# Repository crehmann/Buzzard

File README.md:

# Buzzard

Buzzard is a 40 keys ergonomic split keyboard. The layout is inspired by the [Architeuthis dux](https://github.com/tapioki/cephalopoda/tree/main/Architeuthis%20dux) with pinky, ring, index, and inner columns splayed at 15, 5, 0, -5, -5 degrees. However, it as two additional pinky keys and a modified thumb cluster.

## Features

- Integrated TrackPoint reset circuit and two possible positions to mount a TrackPoint to the bottom of the PCB. Either between the two inner columns or between the index and middle finger columns
- Mounting option for a linear actuator ([HapticBuzz from pimoroni](https://shop.pimoroni.com/products/drv2605l-linear-actuator-haptic-breakout))
- I2C interface for an OLED display
- Wireless Ready (however, without TrackPoint / linear actuator support):
  - Battery switch / connector
  - Option to use a battery friendly Sharp memory display instead of an OLED display
- Choc-spaced
- Partially hot swap sockets supported (not around the TrackPoint  module)
- Either surface mount or through hole components can be used

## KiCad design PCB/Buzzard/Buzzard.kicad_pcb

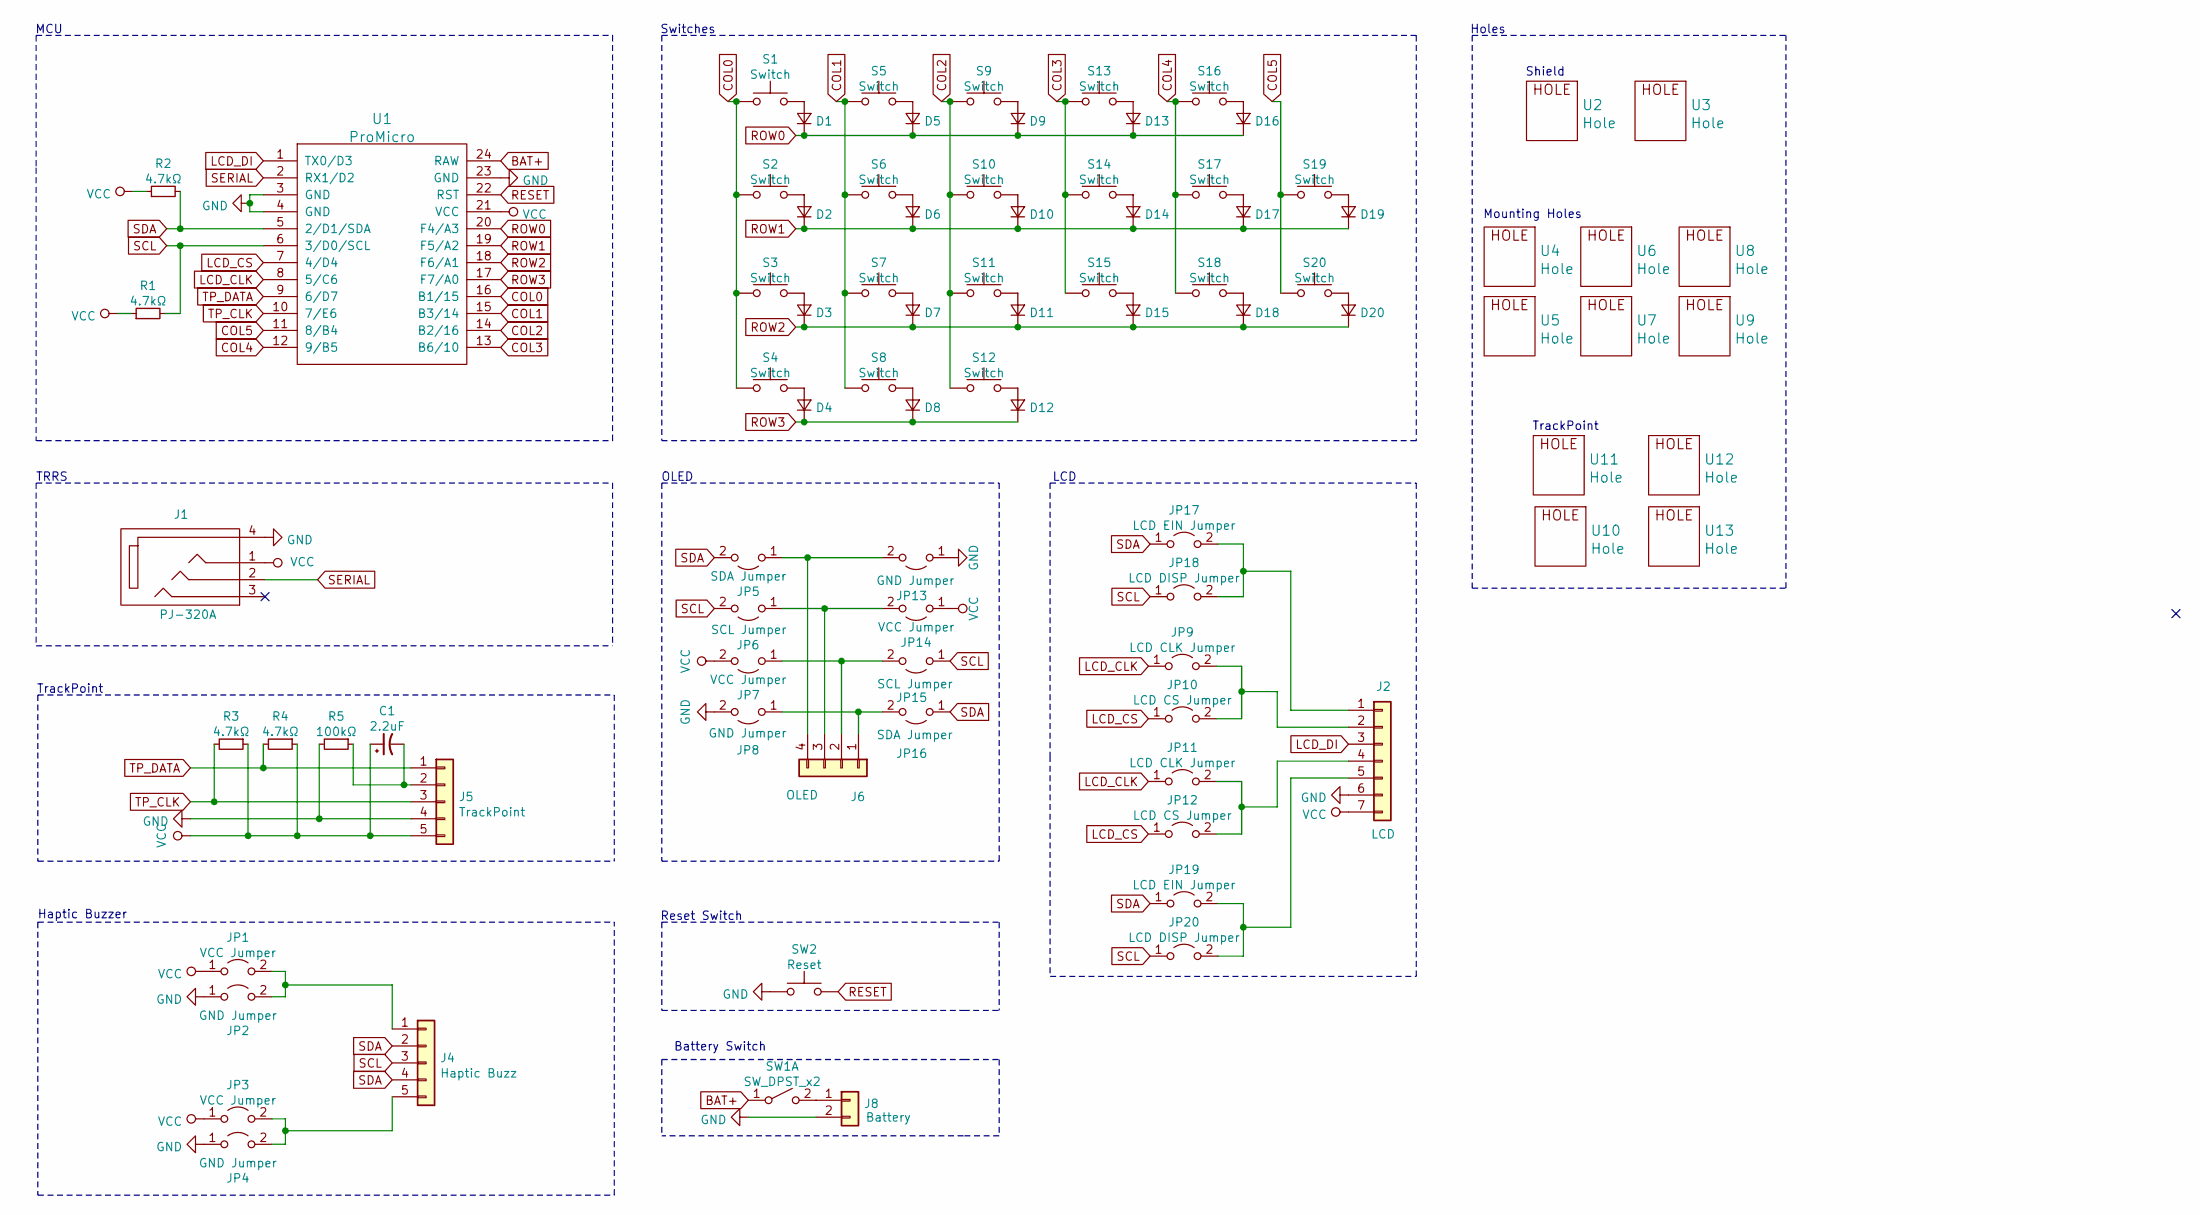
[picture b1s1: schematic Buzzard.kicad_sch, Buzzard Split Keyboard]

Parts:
C1: 2.2uF; C_THT_SMD_0805_HandSolder_Reversable
D1, D2, D3, D4, D5, D6, D7, D8, D9, D10, D11, D12, D13, D14, D15, D16, D17, D18, D19, D20: D_Small; D3_TH_SMD_v2
J1: PJ-320A; MJ-4PP-9
J2: LCD; SharpMemoryLcdBreakout-Reversable
J4: Haptic Buzz; Pimoroni Haptic Buzz DRV2605L Driver
J5: TrackPoint; PinHeader_1x05_P2.54mm_Vertical
J6: OLED
J8: Battery; JST_PH_S2B-PH-K_1x02_P2.00mm_Horizontal
JP1, JP3, JP7, JP14: VCC Jumper; SolderJumper-2_P1.3mm_Open_Pad1.0x1.5mm
JP2, JP4, JP8, JP13: GND Jumper; SolderJumper-2_P1.3mm_Open_Pad1.0x1.5mm
JP5, JP16: SDA Jumper; SolderJumper-2_P1.3mm_Open_Pad1.0x1.5mm
JP6, JP15: SCL Jumper; SolderJumper-2_P1.3mm_Open_Pad1.0x1.5mm
JP9, JP11: LCD CLK Jumper; SolderJumper-2_P1.3mm_Open_Pad1.0x1.5mm
JP10, JP12: LCD CS Jumper; SolderJumper-2_P1.3mm_Open_Pad1.0x1.5mm
JP17, JP19: LCD EIN Jumper; SolderJumper-2_P1.3mm_Open_Pad1.0x1.5mm
JP18, JP20: LCD DISP Jumper; SolderJumper-2_P1.3mm_Open_Pad1.0x1.5mm
R1, R2, R3, R4: 4.7kΩ; Resistor-TH_SMD
R5: 100kΩ; Resistor-TH_SMD
S1, S5, S6, S9, S10: Switch; SW_PG1350_reversible
S2, S3, S4, S7, S8, S11, S12, S13, S14, S15, S16, S17, S18, S19, S20: Switch; Kailh_socket_PG1350_optional_reversible.kicad_mod
SW1: SW_DPST_x2; SW-TH_3P-L9.1-W3.5-P2.50-S3.20-A3
SW2: Reset; SW_Tactile_SPST_Angled_PTS645Vx39-2LFS
U1: ProMicro; ProMicro_v2
U2, U3: Hole; M2_HOLE_PCB
U4, U5, U6, U7, U8, U9, U10, U11, U12, U13: Hole; HOLE_M2_TH

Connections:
BAT+: SW1.1 (A), U1.24 (RAW)
COL0: S1.1, S2.1, S3.1, S4.1, U1.16 (B1/15)
COL1: S5.1, S6.1, S7.1, S8.1, U1.15 (B3/14)
COL2: S9.1, S10.1, S11.1, S12.1, U1.14 (B2/16)
COL3: S13.1, S14.1, S15.1, U1.13 (B6/10)
COL4: S16.1, S17.1, S18.1, U1.12 (9/B5)
COL5: S19.1, S20.1, U1.11 (8/B4)
GND: J1.4, J2.6, J5.4, J8.2, JP2.1 (A), JP4.1 (A), JP8.2 (B), JP13.1 (A), R5.2, SW2.1, U1.3 (GND), U1.4 (GND), U1.23 (GND)
LCD_CLK: JP9.1 (A), JP11.1 (A), U1.8 (5/C6)
LCD_CS: JP10.1 (A), JP12.1 (A), U1.7 (4/D4)
LCD_DI: J2.3, U1.1 (TX0/D3)
unnamed: C1.2, J5.2, R5.1
unnamed: D1.2 (A), S1.2
unnamed: D2.2 (A), S2.2
unnamed: D3.2 (A), S3.2
unnamed: D4.2 (A), S4.2
unnamed: D5.2 (A), S5.2
unnamed: D6.2 (A), S6.2
unnamed: D7.2 (A), S7.2
unnamed: D8.2 (A), S8.2
unnamed: D9.2 (A), S9.2
unnamed: D10.2 (A), S10.2
unnamed: D11.2 (A), S11.2
unnamed: D12.2 (A), S12.2
unnamed: D13.2 (A), S13.2
unnamed: D14.2 (A), S14.2
unnamed: D15.2 (A), S15.2
unnamed: D16.2 (A), S16.2
unnamed: D17.2 (A), S17.2
unnamed: D18.2 (A), S18.2
unnamed: D19.2 (A), S19.2
unnamed: D20.2 (A), S20.2
unnamed: J2.1, JP17.2 (B), JP18.2 (B)
unnamed: J2.2, JP9.2 (B), JP10.2 (B)
unnamed: J2.4, JP11.2 (B), JP12.2 (B)
unnamed: J2.5, JP19.2 (B), JP20.2 (B)
unnamed: J4.1, JP1.2 (B), JP2.2 (B)
unnamed: J4.5, JP3.2 (B), JP4.2 (B)
unnamed: J6.1, JP8.1 (A), JP16.2 (B)
unnamed: J6.2, JP7.1 (A), JP15.2 (B)
unnamed: J6.3, JP6.1 (A), JP14.2 (B)
unnamed: J6.4, JP5.1 (A), JP13.2 (B)
unnamed: J8.1, SW1.2 (B)
RESET: SW2.2, U1.22 (RST)
ROW0: D1.1 (K), D5.1 (K), D9.1 (K), D13.1 (K), D16.1 (K), U1.20 (F4/A3)
ROW1: D2.1 (K), D6.1 (K), D10.1 (K), D14.1 (K), D17.1 (K), D19.1 (K), U1.19 (F5/A2)
ROW2: D3.1 (K), D7.1 (K), D11.1 (K), D15.1 (K), D18.1 (K), D20.1 (K), U1.18 (F6/A1)
ROW3: D4.1 (K), D8.1 (K), D12.1 (K), U1.17 (F7/A0)
SCL: J4.3, JP6.2 (B), JP15.1 (A), JP18.1 (A), JP20.1 (A), R1.2, U1.6 (3/D0/SCL)
SDA: J4.2, J4.4, JP5.2 (B), JP16.1 (A), JP17.1 (A), JP19.1 (A), R2.2, U1.5 (2/D1/SDA)
SERIAL: J1.2, U1.2 (RX1/D2)
TP_CLK: J5.3, R3.2, U1.10 (7/E6)
TP_DATA: J5.1, R4.2, U1.9 (6/D7)
VCC: C1.1, J1.1, J2.7, J5.5, JP1.1 (A), JP3.1 (A), JP7.2 (B), JP14.1 (A), R1.1, R2.1, R3.1, R4.1, U1.21 (VCC)

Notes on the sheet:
MCU
TRRS
TrackPoint
Haptic Buzzer
OLED
Switches
Reset Switch
Battery Switch
LCD
Holes
Shield
Mounting Holes

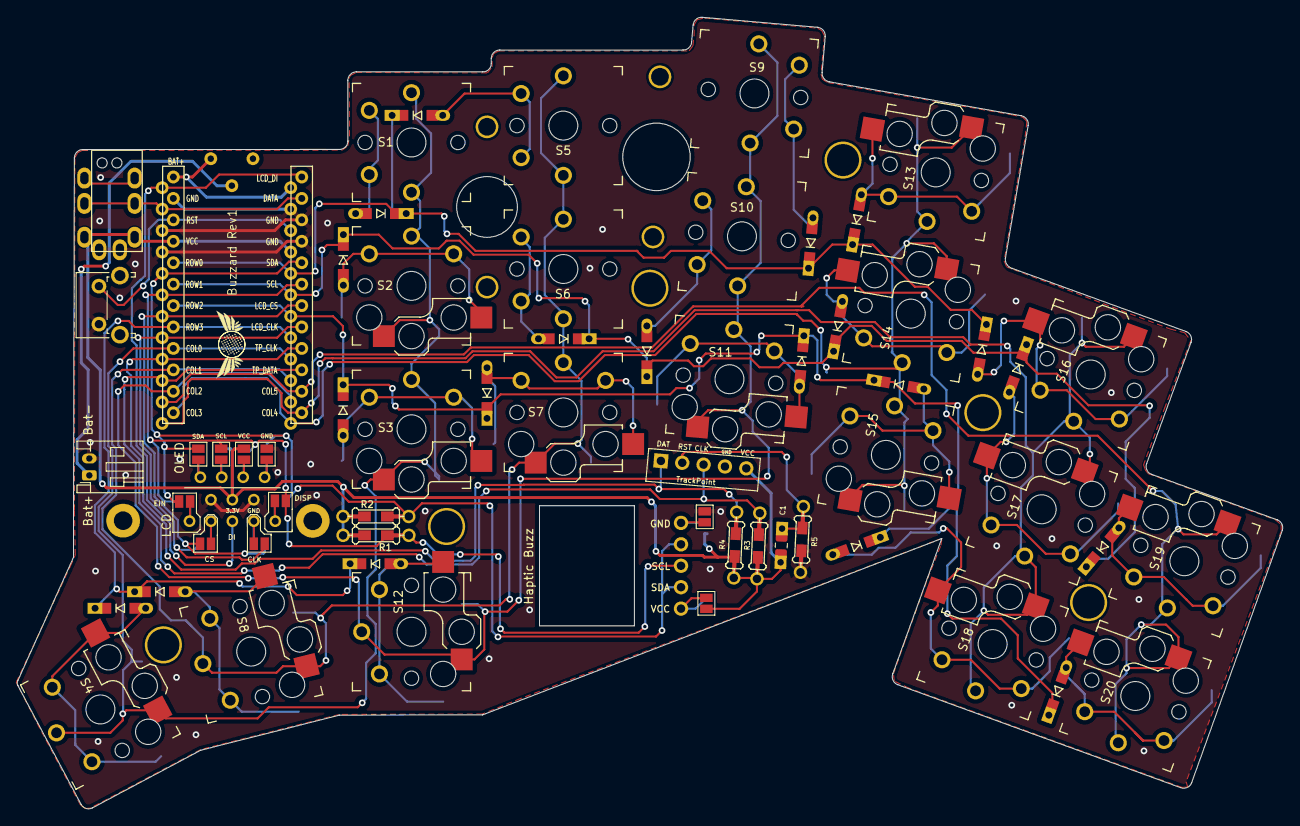
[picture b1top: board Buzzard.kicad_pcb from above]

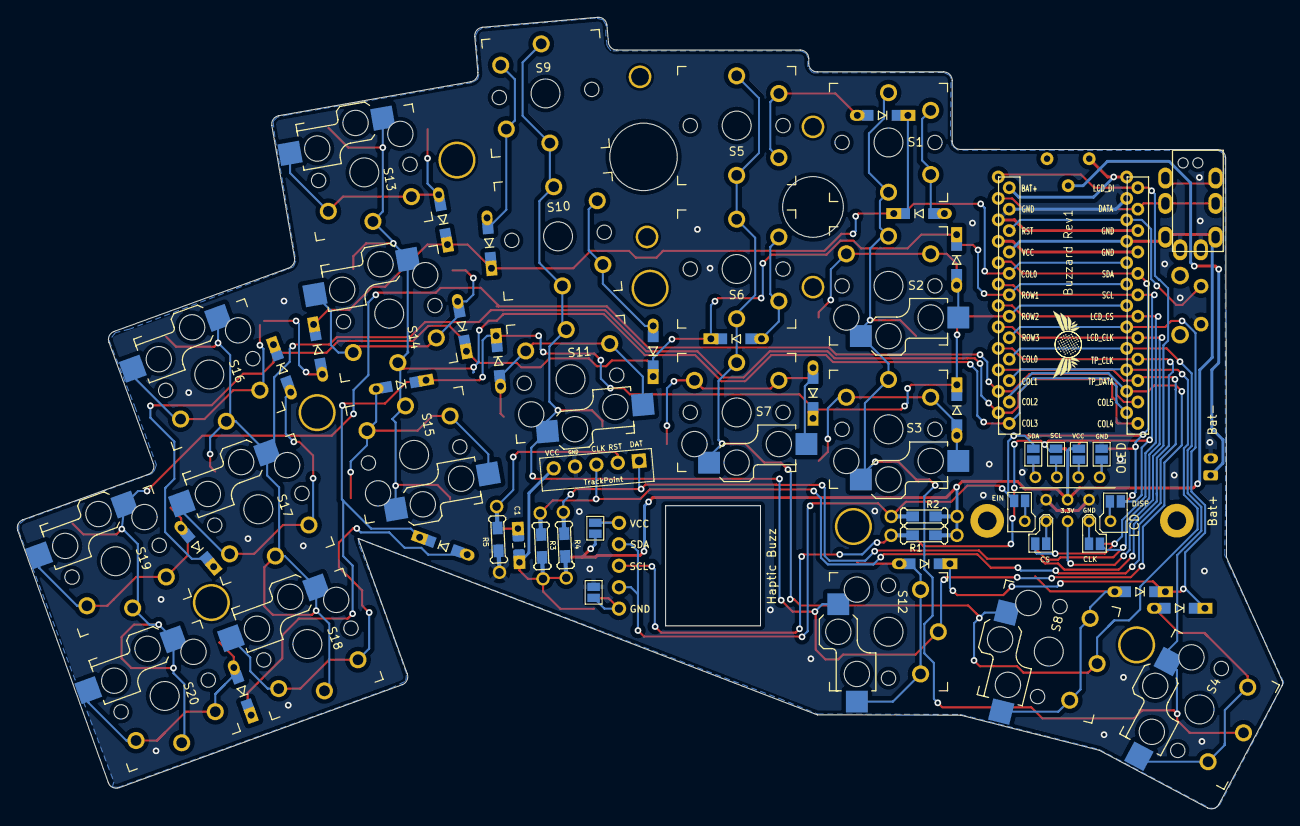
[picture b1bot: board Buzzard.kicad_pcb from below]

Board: 2 copper layers, 150.0 x 93.8 mm, 87 parts (11 on the bottom side), 54 nets.

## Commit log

2021-10-25 add schematics and footprints
2021-10-26 started with pcb design and placed switches
2021-10-27 further work on pcb
2021-10-29 further work on the pcb
2021-10-29 further work
2021-10-31 replaced trrs symbol and fixed connections
2021-10-31 replaced lcd footprint and fixed connections
2021-10-31 placement of trackpoint circuit and thumb cluster
2021-11-01 added mounting holes
2021-11-01 diode placement
2021-11-03 moved mcu and some rework
    moved mcu more to the left
2021-11-03 wiring of switches
2021-11-03 rounded edge cuts
2021-11-03 work on silk screen
2021-11-03 fix errors and warnings
2021-11-03 moved pinky column more to the middle
2021-11-03 adding logo
2021-11-03 added topplate
2021-11-04 add logo and better through holes
2021-11-10 switched trrs lines and TP clock/data lines
2021-11-14 Some fine tuning and silkmask improvments
2021-12-04 added license
2021-12-04 add case render images
2021-12-04 add kicad files for bottom plate
2021-12-04 add readme for top and bottom plate
2021-12-11 added images for build guide
2021-12-11 added guard
2021-12-14 added more pictures
2021-12-14 added note
2021-12-16 add image of schematic
